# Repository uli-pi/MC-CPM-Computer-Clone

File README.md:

# MC-Computer CP/M Computer Clone
 
Hier entsteht ein MC CP/M Computer kompatibler Rechner. Dieser wurde in der Zeitschrift MC Computer 1984 als Nachbauprojekt veröffentlicht. Der Autor war Rolf-Dieter Klein der auch den NDR Computer gleichzeitig entwickelte.
Das Projekt ist als "Retro" Computing Projekt ausgelegt. Die Karten werden nicht 1:1 "gecloned" sondern mit einigen Verbesserungen neu aufgelegt. Es wird aber alles weitgehend mit Chips aus der Zeit aufgebaut werden, also kommen keine SMD Bauteile oder Microcontroller wie Raspi, Arduino oder ähnliches zum Einsatz.

Es werden nachfolgend die Baugruppen CPU Karte (SYS-80s), OUT Karte (OUT-80), Floppy Controller (FLO-80), sowie einige neue Karten hier veröffentlicht. Die Karten sind ECB Bus Kompatibel zu eventuell vorhandenen Karten aus den 80ziger Jahren. Diese können gemischt betrieben werden. Wer also noch einen MC-CPM Computer sein eigen nennt kann z.B. Die CPU Karte gegen die neue SYS-80s tauschen usw.

Die CF Karte ermöglicht den Anschluß eines IDE Kompatiblen Gerätes. Es lassen sich Festplatten, oder auch mit Adapter eine CF Karte ansteuern. Mit dem CF Karten Bios werden 4 Floppy Disk mit jeweils 2MB Kapazität nachgebildet.

Ein minimales CP/M 2.2 System kann mit einer SYS-80s und einer CF-80 Karte aufgebaut werden. Man hat einen vollwertigen Rechner mit einem 60KB CP/M. Oder sie nehmen eine SYS-80s mit einer FLO-80 Karte. Das ergibt einen CP/M Rechner mit richtigen Floppy Laufwerken. Anschluß von 3,5", 5,25" oder 8" ist möglich, auch gemischt je nach Bios.

Mit einer OUT-80 Karte bekommt man zusätzlich 2 serielle und 2 parallele Schnittstellen.

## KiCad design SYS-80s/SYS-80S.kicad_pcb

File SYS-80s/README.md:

# SYS-80s CPU Karte

MC CP/M Computer kompatible CPU Karte zur originalen MC-Computer SYS-1 Karte.

Die SYS-80s Karte hat eine serielle Schnittstelle on Board und benötigt daher zum Betrieb keine  OUT-Karte wie ursprünglich im MC-CP/M Computer vorgesehen. Das Consol Terminal wird direkt an die CPU Karte angeschlossen. Die Einheit kann "Standalone" als vollwertiger Z80 Rechner betrieben werden.

Es gibt ein angepasstes Monitor Eprom (Mon80V1.bin) um diese Schnittstelle als Console zu nutzen. Die SYS-80s kann auch mit dem originalen Monitor Eprom benutzt werden dann ist die Console zur OUT Karte umgeleitet und die "on Board" Schnittstelle frei.

Es ist somit möglich die SYS-80s CPU Karte als 1:1 Ersatz für eine alte SYS-1 zu verwenden wenn diese defekt sein sollte.

Auf der SYS-80 Karte wird ein statisches 128KB RAM verwendet. Der Z80 kann aber nur 64KB adressieren so bleibt die Hälfte des RAM ungenutzt. Der Chip war deutlich preiswerter als andere Lösungen daher wurde er verwendet. Vielleicht ergibt sich ja in Zukunft die Möglichkeit mit einem Hardware "banking" die zweiten 64KB nutzbar zu machen. Der EPROM Sockel erlaubt 4KB oder 8KB Eproms zu benutzen, dies ist per Jumper einstellbar.

Der CPU Takt ist mit einem 12Mhz Quarz zwischen 6Mhz und 3Mhz umschaltbar. Bei Benutzung von 8" Floppy Laufwerken ist 6Mhz erforderlich. Heute gibt es genug Z80 Varianten die schnellen CPU-Takt vertragen.

Der Schnittstellen Chip (D71051C)ist eine schnelle Variante des 8251. Der Chip ist Hard und Software kompatibel. Es lässt sich deshalb auch ein 8251 einsetzen. Während der 8251 bei  Taktraten jenseits 4Mhz Probleme bereitet kann der 71051 bis über 8Mhz getaktet werden.
Die Standard Adresse der seriellen Schnittstelle für das Monitor Eprom (Mon80V1.bin) liegt bei 20H. Per Jumper einstellbar. Mit einem UART Quarz von 4,915 Mhz lässt sich die Übertragung der seriellen Schnittstelle mittels Jumper auf 19,2K Baud, 9,6K Baud und 4,8K Baud einstellen. Mit 2,45Mhz Quarz halbieren sich die Baudraten.

Es gilt weiter die originale Beschreibung der SYS-1 Karte. In dem "Mon80V1" Eprom sind alle Monitor Befehle aus der SYS-1 Beschreibung implementiert. Zusätzlich gibt es 2 Routinen zum lesen und schreiben auf die IDE/CF Schnittstelle für CF Karten. Diese können aber nur aus Programmen über "Call" angesprochen werden.

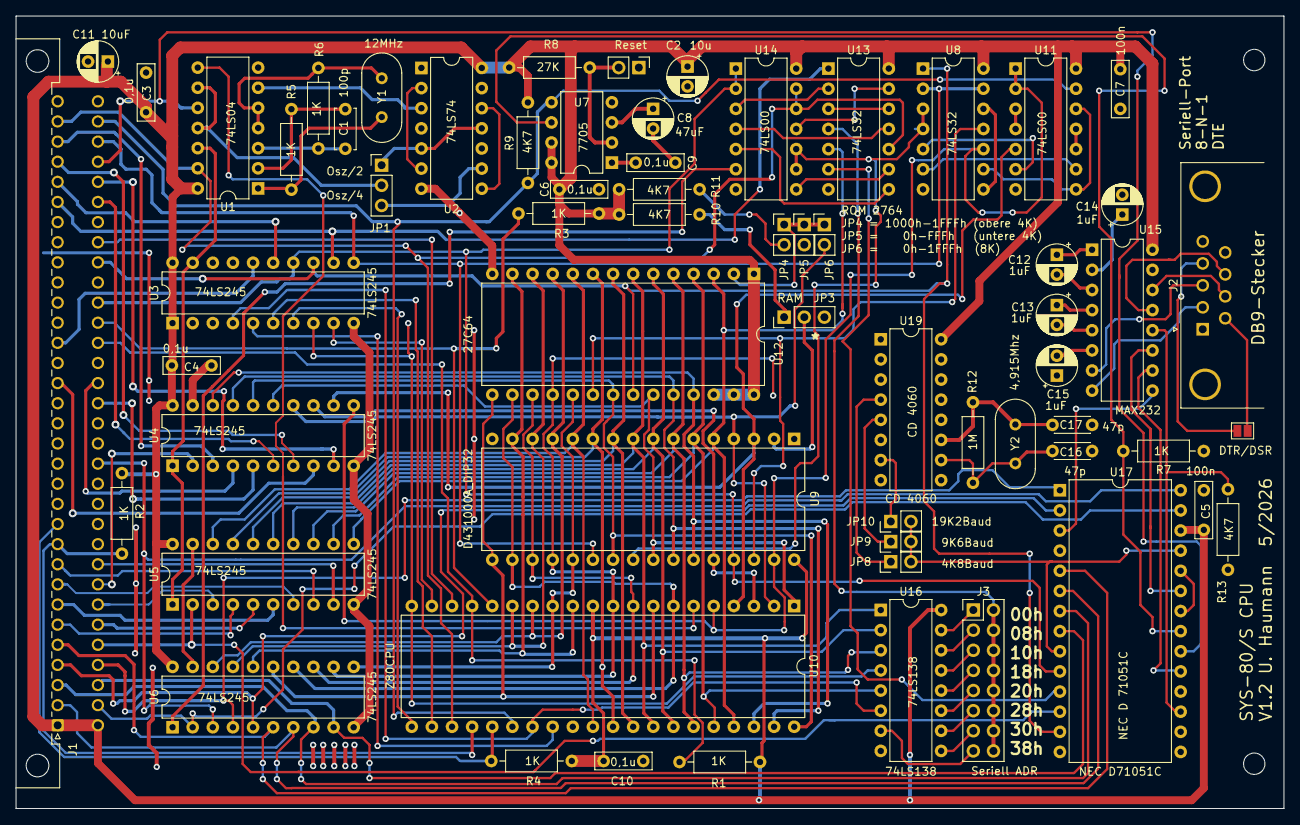
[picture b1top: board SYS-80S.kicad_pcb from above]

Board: 2 copper layers, 160.0 x 100.0 mm, 65 parts (0 on the bottom side), 138 nets.

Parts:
C1: 100p; C_Disc_D5.0mm_W2.5mm_P5.00mm
C2, C11: 10uF; CP_Radial_D5.0mm_P2.50mm
C3, C4, C5, C6, C7, C9, C10: 100n; C_Rect_L7.0mm_W2.0mm_P5.00mm
C8: 47uF; CP_Radial_D5.0mm_P2.50mm
C12, C13, C14, C15: 1uF; CP_Radial_D5.0mm_P2.50mm
C16, C17: 47p; C_Disc_D4.3mm_W1.9mm_P5.00mm
H1, H2: 2,5; MountingHole_2.7mm_M2.5_ISO7380
J1: C64AC; DIN41612_C_2x32_Male_Horizontal_THT
J2: DB9_Male; DSUB-9_Male_Horizontal_P2.77x2.84mm_EdgePinOffset4.94mm_Hou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
J3: ADR-SEL; PinHeader_2x08_P2.54mm_Vertical
JP1, JP3: Jumper_3_Open; PinHeader_1x03_P2.54mm_Vertical
JP2: Reset; PinHeader_1x02_P2.54mm_Vertical
JP4, JP5, JP6, JP8, JP9, JP10: .; PinHeader_1x02_P2.54mm_Vertical
JP7: DTR/DSR; SolderJumper-2_P1.3mm_Open_Pad1.0x1.5mm
R1, R2, R3, R4, R5, R6, R7: 1K; R_Axial_DIN0207_L6.3mm_D2.5mm_P10.16mm_Horizontal
R8: 27K; R_Axial_DIN0207_L6.3mm_D2.5mm_P10.16mm_Horizontal
R9, R10, R11, R13: 4K7; R_Axial_DIN0207_L6.3mm_D2.5mm_P10.16mm_Horizontal
R12: 1M; R_Axial_DIN0207_L6.3mm_D2.5mm_P10.16mm_Horizontal
U1: 74LS04; DIP-14_W7.62mm
U2: 74LS74; DIP-14_W7.62mm
U3, U4, U5, U6: 74LS245; DIP-20_W7.62mm
U7: TL7705A; DIP-8_W7.62mm
U8, U13: 74LS32; DIP-14_W7.62mm
U9: D431000A_DIP32; DIP-32_W15.24mm
U10: Z80CPU; DIP-40_W15.24mm
U11, U14: 74LS00; DIP-14_W7.62mm
U12: 27C64; DIP-28_W15.24mm
U15: MAX232; DIP-16_W7.62mm
U16: 74LS138; DIP-16_W7.62mm
U17: NEC D71051C; DIP-28_W15.24mm
U19: CD 4060; DIP-16_W7.62mm
Y1: 16MHz; Crystal_HC18-U_Vertical
Y2: 4,915Mhz; Crystal_HC18-U_Vertical

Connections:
+5V: C2.1, C3.2, C4.2, C5.2, C6.2, C7.2, C10.2, C11.1, J1.A1, J1.C1, R1.1, R2.1, R3.1, R4.1, R8.2, R9.1, R10.2, R11.2, U1.14, U2.14, U3.1, U3.20, U4.20, U5.20, U6.20, U7.7, U7.8, U8.14, U9.32, U10.11, U11.14, U12.1, U12.26, U12.27, U12.28, U13.14, U14.14, U15.16, U16.16, U17.26, U19.16
+RESET: R7.2, U7.6, U17.21
-BUSAK: J1.A31, U1.13, U10.23, U13.10, U14.12, U14.13
-BUSRQ: J1.A11, R4.2, U10.25
-CS-RAM: U8.3, U8.4, U9.24, U14.9, U14.10
-CS-ROM: U8.11, U9.30, U12.20
-HALT: J1.C25, U10.18
-INT: J1.C21, R3.2, U10.16
-IORQv: J1.A27, U3.12, U13.1
-M1v: J1.A20, U3.16
-MREQv: J1.C30, U3.11, U8.2, U8.13, U9.22
-NMI: J1.C20, R1.2, U10.17
-RDv: J1.C24, U3.13, U8.1, U12.22, U17.13
-RESET: J1.C31, R9.2, U7.5, U10.26, U11.13
-RFSHv: J1.A28, U3.15
-WAIT: J1.A10, R2.2, U10.24
-WRv: J1.C22, U3.14, U9.29, U14.1, U14.2, U17.10
A0: U5.18, U9.12, U10.30, U12.10
A0v: J1.C5, U5.2, U17.12
A1: U5.17, U9.11, U10.31, U12.9
A1v: J1.C7, U5.3
A2: U5.16, U9.10, U10.32, U12.8
A2v: J1.A6, U5.4
A3: U5.15, U9.9, U10.33, U12.7, U16.1
A3v: J1.C6, U5.5
A4: U5.14, U9.8, U10.34, U12.6, U16.2
A4v: J1.A7, U5.6
A5: U5.13, U9.7, U10.35, U12.5, U16.3
A5v: J1.A8, U5.7
A6: U5.12, U9.6, U10.36, U12.4, U16.5
A6v: J1.A9, U5.8
A7: U5.11, U9.5, U10.37, U12.3, U13.5
A7v: J1.C9, U5.9
A8: U4.18, U9.27, U10.38, U12.25
A8v: J1.C8, U4.2
A9: U4.17, U9.26, U10.39, U12.24
A9v: J1.A30, U4.3
A10: U4.16, U9.23, U10.40, U12.21
A10v: J1.C18, U4.4
A11: U4.15, U9.25, U10.1, U12.23
A11v: J1.C17, U4.5
A12: JP6.2, U4.14, U9.4, U10.2
A12v: J1.C27, U4.6
A13: U4.13, U9.28, U10.3
A13v: J1.A29, U4.7
A14: U4.12, U9.3, U10.4, U11.5
A14v: J1.A18, U4.8
A15: U4.11, U8.10, U9.31, U10.5, U11.1, U11.2
A15v: J1.C28, U4.9
BAUD: JP8.2, JP9.2, JP10.2, U17.9, U17.25
BUSAK: U1.12, U3.19, U4.1, U5.1
CLK: U1.8, U10.6
CTS: R13.1, U15.12, U17.17
D0: U6.18, U9.13, U10.14, U12.11
D0v: J1.C2, U6.2, U17.27
D1: U6.17, U9.14, U10.15, U12.12
D1v: J1.C14, U6.3, U17.28
D2: U6.16, U9.15, U10.12, U12.13
D2v: J1.C4, U6.4, U17.1
D3: U6.15, U9.17, U10.8, U12.15
D3v: J1.A4, U6.5, U17.2
D4: U6.14, U9.18, U10.7, U12.16
D4v: J1.A5, U6.6, U17.5
D5: U6.13, U9.19, U10.9, U12.17
D5v: J1.A2, U6.7, U17.6
D6: U6.12, U9.20, U10.10, U12.18
D6v: J1.A3, U6.8, U17.7
D7: U6.11, U9.21, U10.13, U12.19
D7v: J1.C3, U6.9, U17.8
GND: C2.2, C3.1, C4.1, C5.1, C6.1, C7.1, C8.2, C9.1, C10.1, C11.2, C14.2, C15.1, C16.1, C17.1, J1.A32, J1.C32, J2.5, JP2.1, JP3.3, JP5.2, R7.1, R13.2, U1.7, U2.7, U3.10, U4.10, U4.19, U5.10, U5.19, U6.10, U6.19, U7.4, U8.7, U9.16, U10.29, U11.7, U12.14, U13.7, U14.7, U15.15, U16.8, U17.4, U19.8, U19.12
IO-Data: U6.1, U14.6
IORQ*: U3.8, U10.20, U16.4
M1*: U3.4, U10.27, U16.6
MREQ*: U3.9, U10.19
unnamed: C1.1, R6.2, U1.3
unnamed: C1.2, R5.1, U1.2
unnamed: C8.1, U7.3
unnamed: C9.2, U7.1
unnamed: C12.1, U15.1
unnamed: C12.2, U15.3
unnamed: C13.1, U15.4
unnamed: C13.2, U15.5
unnamed: C14.1, U15.2
unnamed: C15.2, U15.6
unnamed: C16.2, R12.1, U19.10, Y2.1
unnamed: C17.2, R12.2, U19.11, Y2.2
unnamed: J2.2, U15.8
unnamed: J2.3, U15.7
unnamed: J2.4, JP7.2
unnamed: J2.6, JP7.1
unnamed: J2.7, U15.14
unnamed: J2.8, U15.13
unnamed: J3.1, U16.15
unnamed: J3.3, U16.14
unnamed: J3.5, U16.13
unnamed: J3.7, U16.12
unnamed: J3.9, U16.11
unnamed: J3.2, J3.4, J3.6, J3.8, J3.10, J3.12, J3.14, J3.16, U13.4
unnamed: J3.11, U16.10
unnamed: J3.13, U16.9
unnamed: J3.15, U16.7
unnamed: JP1.1, U2.5, U2.11
unnamed: JP1.2, U1.9, U1.11
unnamed: JP1.3, U2.9
unnamed: JP2.2, R8.1, U7.2
unnamed: JP3.1, R10.1
unnamed: JP3.2, U9.2
unnamed: JP4.1, JP5.1, JP6.1, U12.2
unnamed: JP4.2, R11.1
unnamed: JP8.1, U19.4
unnamed: JP9.1, U19.5
unnamed: JP10.1, U19.7
unnamed: R5.2, U1.1, Y1.1
unnamed: R6.1, U1.4, U1.5, Y1.2
unnamed: U1.6, U2.3
unnamed: U2.2, U2.6
unnamed: U2.8, U2.12
unnamed: U8.8, U8.12
unnamed: U11.3, U11.4
unnamed: U8.5, U11.6
unnamed: U8.6, U11.9
unnamed: U11.10, U11.11
unnamed: U8.9, U11.8, U11.12
unnamed: U13.2, U14.3
unnamed: U13.8, U14.5
unnamed: U13.9, U14.8
unnamed: U13.11, U14.4
unnamed: U13.3, U13.12
unnamed: U13.13, U14.11
unnamed: U17.22, U17.24
PHI: J1.C29, U1.10, U17.20
RD*: U3.7, U10.21
RFSH*: U3.5, U10.28
RTS: U15.11, U17.23
RXD: U15.9, U17.3
TXD: U15.10, U17.19
UART-CS: U13.6, U17.11
WR*: U3.6, U10.22

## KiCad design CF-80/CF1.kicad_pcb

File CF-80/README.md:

# CF-80 Karte 

Die Karte wurde für das MC-Computer ECB Bus System entwickelt und verwendet nur 8 Bit des angeschlossenen 16Bit Mediums. Das halbiert schon einmal vorweg die nutzbare Kapazität. Es sollte ein Datenträger mit mindestens 128MB verwendet werden.
Es kann auch eine ATA  oder eine SSD Festplatte verwendet werden.
 
Anschluss eines Laufwerks:

Diese Karte funktioniert mit den meisten IDE/CF/SSD-Laufwerken. Die Kapazität des Laufwerks sollte 128 Megabyte oder mehr betragen, wenn Sie CP/M installieren möchten. Dies ist nicht erforderlich, um genügend Speicherplatz zu haben – denn ein vollwertiges CP/M-System belegt unter 1 MB an Speicherplatz –, sondern vielmehr weil die von mir verwendeten Treiber vereinfachten Code verwenden, der den Speicherplatz nicht sehr effizient nutzt. Es kommt eine vereinfachte Arithmetik zum Einsatz, um die CP/M-Sektoren auf die LBA-Sektoren der Festplatte abzubilden. Dabei bleibt ein erheblicher Teil des Speicherplatzes ungenutzt.  Es kann aber jeder einen Treiber selbst für das System schreiben um den Speicherplatz auszunutzen. 
Viele kleine Solid-State-Flash-Module benötigen keinen separaten Stromanschluss; stattdessen können Sie die +5V-Spannung (bei geringer Stromaufnahme) direkt über Pin 20 des Laufwerksanschlusses beziehen. Bei der vorliegenden Karte liegt dieser auf +5V und die SSD bzw. CF Karten benötigen daher keine externe Spannungsversorgung.

Die Adressen sind auf der Karte zwischen 010h bis 078h einstellbar, es werden 8 Adressen benutzt.
Für das SYS-80 System liegt die Basis Adresse auf 018Hex.

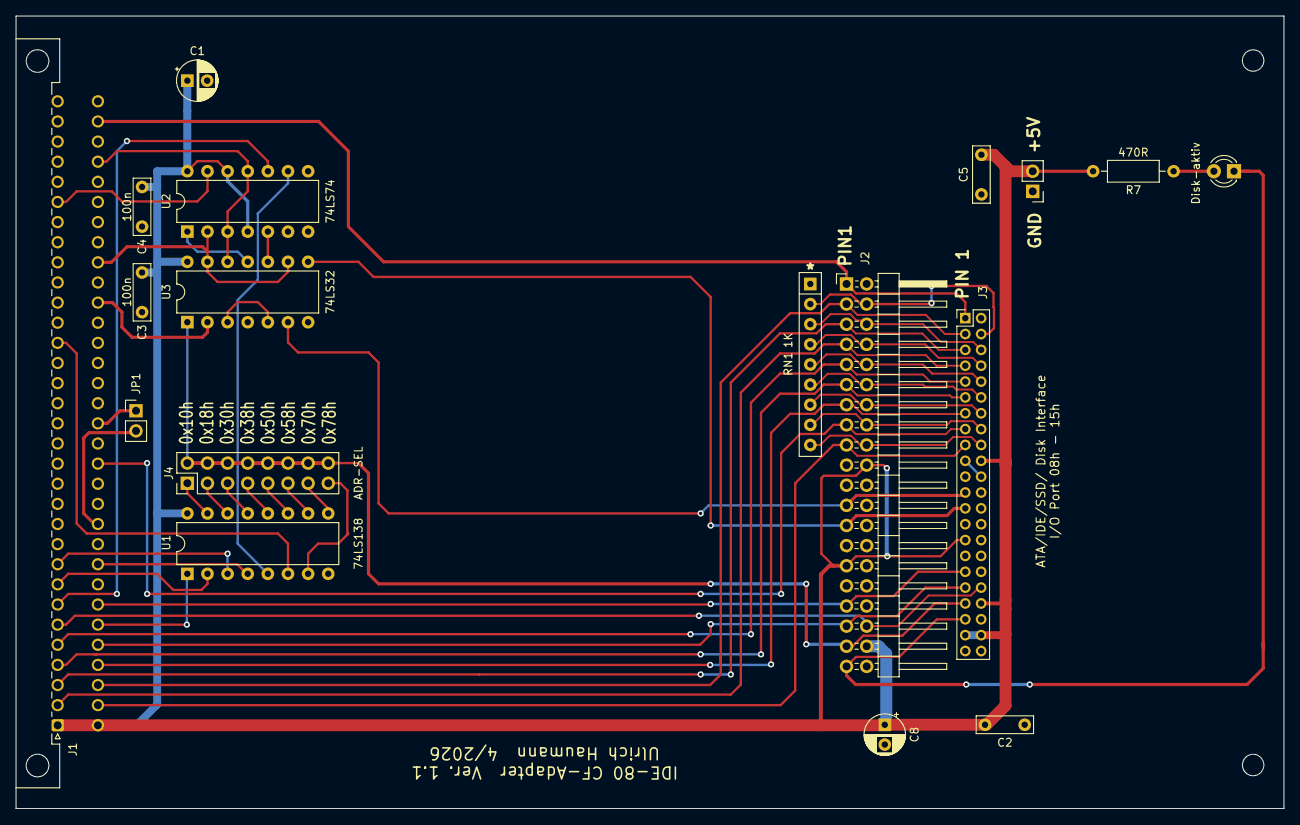
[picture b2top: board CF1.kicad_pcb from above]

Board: 2 copper layers, 160.0 x 100.0 mm, 20 parts (0 on the bottom side), 51 nets.

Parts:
C1, C8: 10uF; CP_Radial_D5.0mm_P2.50mm
C2, C3, C4, C5: 100n; C_Rect_L7.0mm_W2.0mm_P5.00mm
D2: Disk-aktiv; LED_D3.0mm
H1, H2: MountingHole; MountingHole_2.7mm_M2.5
J1: C64AC; DIN41612_C_2x32_Male_Horizontal_THT
J2: IDE-40; PinHeader_2x20_P2.54mm_Horizontal
J3: IDE-44; PinHeader_2x22_P2.00mm_Vertical
J4: ADR-SEL; PinHeader_2x08_P2.54mm_Vertical
JP1, JP4: .; PinHeader_1x02_P2.54mm_Vertical
R7: 470R; R_Axial_DIN0207_L6.3mm_D2.5mm_P10.16mm_Horizontal
RN1: 1K; R_Array_SIP9
U1: 74LS138; DIP-16_W7.62mm
U2: 74LS74; DIP-14_W7.62mm
U3: 74LS32; DIP-14_W7.62mm

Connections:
+5V: C1.1, C2.2, C3.2, C4.2, C5.2, C8.1, J1.A1, J1.C1, J2.20, J2.29, J2.38, J3.20, J3.29, J3.38, J3.41, J3.42, JP4.2, R7.2, U1.16, U2.4, U2.12, U2.14, U3.14
-CS1-DSK: J2.37, J3.37, J4.2, J4.4, J4.6, J4.8, J4.10, J4.12, J4.14, J4.16, U3.1
-IORQv: J1.A27, U2.13
-M1v: J1.A20, U1.6
-RDv: J1.C24, U2.2, U3.9, U3.13
-RESET: J1.C31, J2.1, J3.1
-WRv: J1.C22, U3.2
A0v: J1.C5, J2.35, J3.35
A1v: J1.C7, J2.33, J3.33
A2v: J1.A6, J2.36, J3.36
A3v: J1.C6, U1.1
A4v: J1.A7, U2.10
A5v: J1.A8, U1.2
A6v: J1.A9, U1.3
A7v: J1.C9, U1.4
CLK: J1.C29, U2.3, U2.11, U3.12
D0v: J1.C2, J2.17, J3.17
D1v: J1.C14, J2.15, J3.15
D2v: J1.C4, J2.13, J3.13
D3v: J1.A4, J2.11, J3.11
D4v: J1.A5, J2.9, J3.9
D5v: J1.A2, J2.7, J3.7
D6v: J1.A3, J2.5, J3.5
D7v: J1.C3, J2.3, J3.3
GND: C1.2, C2.1, C3.1, C4.1, C5.1, C8.2, J1.A32, J1.C32, J2.2, J2.19, J2.22, J2.24, J2.26, J2.30, J2.40, J3.2, J3.19, J3.22, J3.24, J3.26, J3.30, J3.40, J3.43, JP4.1, RN1.1, U1.8, U2.7, U3.4, U3.7
IEI: J1.C11, JP1.2
IEO: J1.C16, JP1.1
IORD*: J2.25, J3.25, U3.8
IOWR*: J2.23, J3.23, U3.6
unnamed: D2.1, J2.39, J3.39
unnamed: D2.2, R7.1
unnamed: J4.1, U1.15
unnamed: J4.3, U1.14
unnamed: J4.5, U1.13
unnamed: J4.7, U1.12
unnamed: J4.9, U1.11
unnamed: J4.11, U1.10
unnamed: J4.13, U1.9
unnamed: J4.15, U1.7
unnamed: U1.5, U2.9
unnamed: U2.1, U3.11
unnamed: U2.5, U3.10
unnamed: U3.3, U3.5
RGND1: J2.4, J3.4, RN1.2
RGND2: J2.6, J3.6, RN1.3
RGND3: J2.8, J3.8, RN1.4
RGND4: J2.10, J3.10, RN1.5
RGND5: J2.12, J3.12, RN1.6
RGND6: J2.14, J3.14, RN1.7
RGND7: J2.16, J3.16, RN1.8
RGND8: J2.18, J3.18, RN1.9

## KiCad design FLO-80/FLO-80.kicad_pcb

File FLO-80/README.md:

# Floppy Controller FLO-80

Die Flo-80 Karte ist kompatibel zur FLO-2 Karte des MC CP/M Computers. 
Es wurde der FDC9239BT Datenseparator benutzt da die alte originale FLO-Karte erhebliche Probleme mit dem Datenseparator hatte. In der ersten FLO Karte war der Datenseparator noch diskret aufgebaut und ohne Oszilloskope war ein Abgleich nur schwer möglich. Dann gab es eine Umbauanleitung mit dem 9216 Datenseparator. Die folgenden FLO Karten verwendeten den FDC 9229 Chip.
 
Auf den FLO-80 Karten können FDC9239BT oder FDC9229BT bestückt werden, je nachdem welcher Chip erhältlich ist. Dies ist mit 2 Jumpern einstellbar.
 
Für den FDC9229BT ist zwingend der Quarzoszillator X1 erforderlich. Beim FDC9239BT kann anstelle des X1 auch der Quarz Y1 eingesetzt werden.

Es sind Pfostenstecker für 3,5" bzw.  5,25" und 8" Laufwerke vorhanden. Die Dekodierung erlaubt den direkten Anschluss von 4 Laufwerken. Modere PC Laufwerke haben meist  keinen "READY" Anschluss mehr, da der PC heute stattdessen den Disk Change Anschluss benutzt. Manche Laufwerke können mittels Jumper auf die Signale eingestellt werden. Bei dem größten Teil der Laufwerke ist dies aber nicht oder nur mit Eingriff in die Elektronik möglich. Der Floppy Controller Chip benötigt aber dieses Signal, daher kann die FLO-80 Karte Ihr eigenes Ready Signal erzeugen. Hierzu sind die Jumper DS1 bis DS4 Vorgesehen. Somit können alle Laufwerke verwendet werden.
Mittels Adapter ist es möglich 3,5" Laufwerke anzuschließen.  Man benötigt ein 1:1 Kabel. Bei einem gedrehten PC Floppy Anschlusskabel muss man den Stecker für das zweite Laufwerk von dem gedrehten Teil auf den geraden Teil umklemmen. Auf dem Adapter ist die ID für Disk 1 bis 4 (entspricht Laufwerk A bis D) per Jumper einstellbar.

3,5" Disk Laufwerke sind heute noch gut zu bekommen und lassen sich im MC-Computer nutzen.
Wird bei  3,5" Disketten das HD "Loch" zugeklebt, sind die Disketten als DD Disketten nutzbar. Diese können dann mit NDR Format formatiert und als 800KB Disketten genutzt werden. 
Es gilt weiterhin die originale Beschreibung der FLO2 Karte.

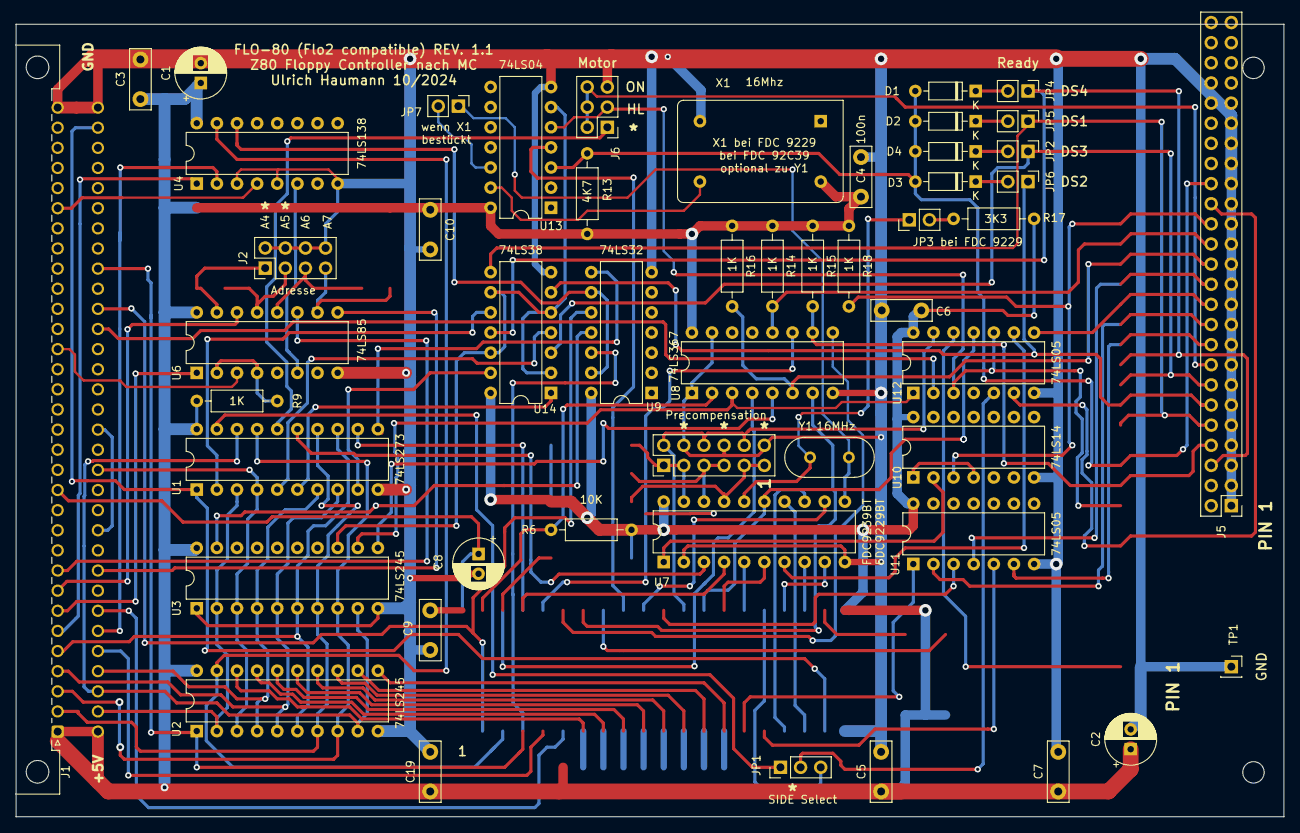
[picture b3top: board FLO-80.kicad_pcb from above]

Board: 2 copper layers, 160.0 x 100.0 mm, 53 parts (0 on the bottom side), 81 nets.

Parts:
C1, C2, C8: 10u; CP_Radial_D6.3mm_P2.50mm
C3, C4, C5, C6, C7, C9, C10, C19: 100n; C_Disc_D7.5mm_W2.5mm_P5.00mm
D1, D2, D3, D4: 1N4148; D_DO-35_SOD27_P7.62mm_Horizontal
H1, H2: 2,7; MountingHole_2.7mm
J1: C64AC; DIN41612_C_2x32_Male_Horizontal_THT
J2: Adresse; PinHeader_2x04_P2.54mm_Vertical
J3: Precomp; PinHeader_2x06_P2.54mm_Vertical
J5: 5,25; PinHeader_2x17_P2.54mm_Vertical
J6: Motor ON; PinHeader_2x03_P2.54mm_Vertical
JP1: Side; PinHeader_1x03_P2.54mm_Vertical
JP2, JP3, JP4, JP5, JP6, JP7: Jumper; PinHeader_1x02_P2.54mm_Vertical
R6: 10K; R_Axial_DIN0207_L6.3mm_D2.5mm_P10.16mm_Horizontal
R9, R14, R15, R16, R18: 1K; R_Axial_DIN0207_L6.3mm_D2.5mm_P10.16mm_Horizontal
R13: 4K7; R_Axial_DIN0207_L6.3mm_D2.5mm_P10.16mm_Horizontal
R17: 3K3; R_Axial_DIN0207_L6.3mm_D2.5mm_P10.16mm_Horizontal
TP1: TestPoint; PinSocket_1x01_P2.54mm_Vertical
U1: 74LS273; DIP-20_W7.62mm
U2, U3: 74LS245; DIP-20_W7.62mm
U4: 74LS138; DIP-16_W7.62mm
U6: 74LS85; DIP-16_W7.62mm
U7: FDC9239BT; DIP-20_W7.62mm
U8: 74LS367; DIP-16_W7.62mm
U9: 74LS32; DIP-14_W7.62mm
U10: 74LS14; DIP-14_W7.62mm
U11, U12: 74LS05; DIP-14_W7.62mm
U13: 74LS04; DIP-14_W7.62mm
U14: 74LS38; DIP-14_W7.62mm
X1: 16Mhz; Oscillator_DIP-14
Y1: 16MHz; Crystal_HC18-U_Vertical

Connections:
+5V: C1.1, C2.1, C3.1, C4.1, C5.1, C6.1, C7.1, C10.1, C19.1, J1.A1, J1.C1, R6.1, R9.1, R13.1, R14.1, R15.1, R16.1, R17.1, R18.1, U1.20, U2.20, U3.20, U4.16, U6.16, U7.20, U8.16, U9.14, U10.14, U11.14, U12.14, U13.14, U14.14, X1.14
+12V: C8.1, C9.1, J1.A13
A2: J1.A6, U4.1
A3: J1.C6, U4.2
A4: J1.A7, U6.1
A5: J1.A8, U6.14
A6: J1.A9, U6.11
A7: J1.C9, U6.9
CS_U3: U4.14, U9.9, U9.13
D0: J1.C2, U1.3, U2.2, U3.2
D1: J1.C14, U1.4, U2.3, U3.3
D2: J1.C4, U1.7, U2.4, U3.4
D3: J1.A4, U1.8, U2.5, U3.5
D4: J1.A5, U1.13, U2.6, U3.6
D5: J1.A2, U1.14, U2.7, U3.7
D6: J1.A3, U1.17, U2.8, U3.8
D7: J1.C3, U1.18, U2.9, U3.9
DIRC: J5.34, U11.6
DS1: J5.26, JP5.1, U14.8
DS2: J5.28, JP6.1, U14.6
DS3: J5.30, JP2.1, U14.3
DS4: J5.32, JP4.1, U14.11
GND: C1.2, C2.2, C3.2, C4.2, C5.2, C6.2, C7.2, C8.2, C9.2, C10.2, C19.2, J1.A32, J1.C32, J2.2, J2.4, J2.6, J2.8, J3.4, J3.8, J3.12, J5.1, J5.3, J5.5, J5.7, J5.9, J5.11, J5.13, J5.15, J5.17, J5.19, J5.21, J5.23, J5.25, J5.27, J5.29, J5.31, J5.33, J5.35, J5.37, J5.39, J5.41, J5.43, J5.45, J5.47, J5.49, J6.5, TP1.1, U1.10, U2.10, U3.1, U3.10, U4.3, U4.5, U4.8, U6.8, U7.2, U7.10, U8.1, U8.8, U8.15, U9.7, U10.7, U11.7, U12.7, U13.7, U14.7, X1.7
HEADLOAD: J5.18, J6.3, U12.3, U12.10, U13.5
HLD_F: U7.15, U12.11
INDEX: J5.20, R15.2, U8.10
L-0: U1.2, U14.10
L-1: U1.5, U14.4
L-2: U1.6, U14.1
L-3: U1.9, U14.13
L-6: J6.1, U1.16
L-7: JP1.1, U1.19
MOTORON: J6.2, J6.4, J6.6
unnamed: D1.1, JP4.2
unnamed: D2.1, JP5.2
unnamed: D3.1, JP6.2
unnamed: D4.1, JP2.2
unnamed: J1.C11, J1.C16
unnamed: J2.1, U6.15
unnamed: J2.3, U6.13
unnamed: J2.5, U6.12
unnamed: J2.7, U6.10
unnamed: J3.1, J3.3, U7.19
unnamed: J3.5, J3.7, U7.18
unnamed: J3.9, J3.11, U7.17
unnamed: JP1.2, U12.5
unnamed: JP3.1, U7.16, Y1.2
unnamed: JP3.2, R17.2
unnamed: JP7.1, U7.11, Y1.1
unnamed: JP7.2, U13.12
unnamed: R6.2, U8.2
unnamed: R9.2, U6.2, U6.4
unnamed: U1.11, U9.8
unnamed: U1.12, U7.4
unnamed: U1.15, U7.3
unnamed: U2.19, U4.15
unnamed: U3.11, U8.5
unnamed: U3.19, U9.11
unnamed: U4.6, U6.6
unnamed: U10.1, U10.4
unnamed: U3.12, U8.3, U12.1
unnamed: U3.13, U13.6, U14.2, U14.5, U14.9, U14.12
unnamed: U13.13, X1.8
RAWIN: U7.1, U10.2
RAWRQ: J5.46, R18.2, U10.3
READY: D1.2, D2.2, D3.2, D4.2, J5.22, R13.2, U13.3
SIDE: J5.14, U12.6
STEP: J5.36, U11.2
TG43: J5.2, U12.12
TG43-F: J3.2, J3.6, J3.10, U12.13
TK0: J5.42, R16.2, U8.6
WDATA: J5.38, U12.8
WDOUT: U7.7, U12.9
WG: J5.40, U11.4
WRTPT: J5.44, R14.2, U8.12
~INT: J1.C21, U12.2
~IOREQ: J1.A27, U4.4
~M1: J1.A20, U6.3
~RD: J1.C24, U2.1, U9.12
~RESET: J1.C31, U1.1
~WR: J1.C22, U9.10

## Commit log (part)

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2026-05-15 bilder
2026-05-15 MC-Computer
2026-05-15 Update README.md
    Kleine Textkorrektur (als Test)
2026-05-16 KiCad-Files
2026-05-19 Backplanes, Floppyadapter
    8er und 5er Backplane
    3,5" Floppyadapter
2026-05-19 Floppy-Adapter Schaltplan
2026-05-19 BUS-80-8 Schaltplan und Foto
2026-05-19 Busboard Images
2026-05-20 Update
    Update 20.05.2026
2026-05-22 update Disk
2026-05-22 file update
2026-05-31 Quelltext für uformat 1.22
2026-06-05 Mon80V2
2026-06-06 Update Mon80V2
2026-06-22 UFORMAT 1.22
2026-06-25 bios31 hinzugefügt
2026-06-30 Update load80.z80
    Falscher ORG-Befehl in load80.z80
2026-06-30 Quelltext für SYSGEN80 zugefügt
